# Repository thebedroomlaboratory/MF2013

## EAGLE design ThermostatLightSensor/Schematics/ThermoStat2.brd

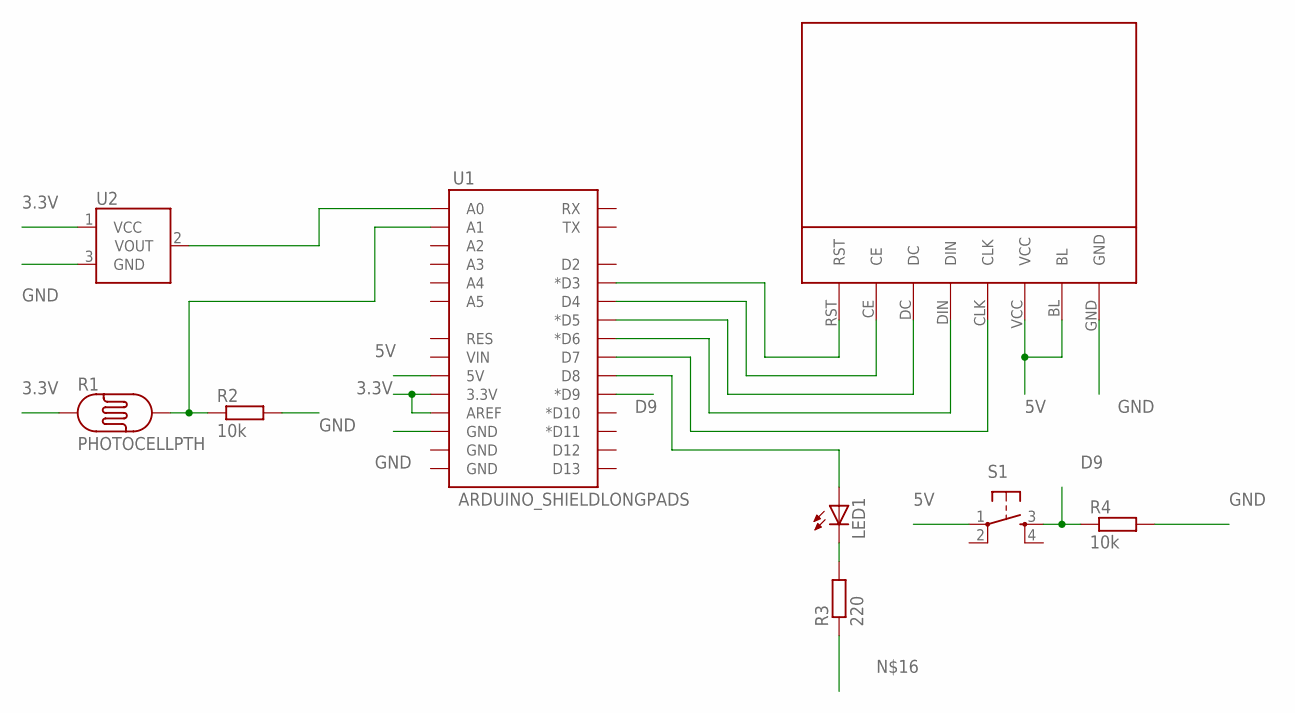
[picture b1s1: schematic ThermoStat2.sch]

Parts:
LED1: LED5MM
R1: PHOTOCELLPTH; PHOTOCELL
R2, R4: 10k; 0207/15
R3: 220; 0207/15
S1: TAC_SWITCHPTH; TACTILE-PTH
U1: ARDUINO_SHIELDLONGPADS; DUEMILANOVE_SHIELD_LONGPADS
U2: TMP36GT9; TO-92
U$1: NOKIA5510

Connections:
3.3V: R1.1, U1.3.3V, U1.AREF, U2.1 (VCC)
5V: S1.1, U1.5V, U$1.BL, U$1.VCC
D9: R4.1, S1.3, U1.D9 (*D9)
GND: R2.2, R4.2, U1.GND@2 (GND), U2.3 (GND), U$1.GND
unnamed: R1.2, R2.1, U1.A1
unnamed: U1.A0, U2.2 (VOUT)
unnamed: U1.D3 (*D3), U$1.RST
unnamed: U1.D4, U$1.CE
unnamed: U1.D5 (*D5), U$1.DC
unnamed: U1.D6 (*D6), U$1.DIN
unnamed: U1.D7, U$1.CLK
unnamed: LED1.K (C), R3.2
unnamed: LED1.A, U1.D8

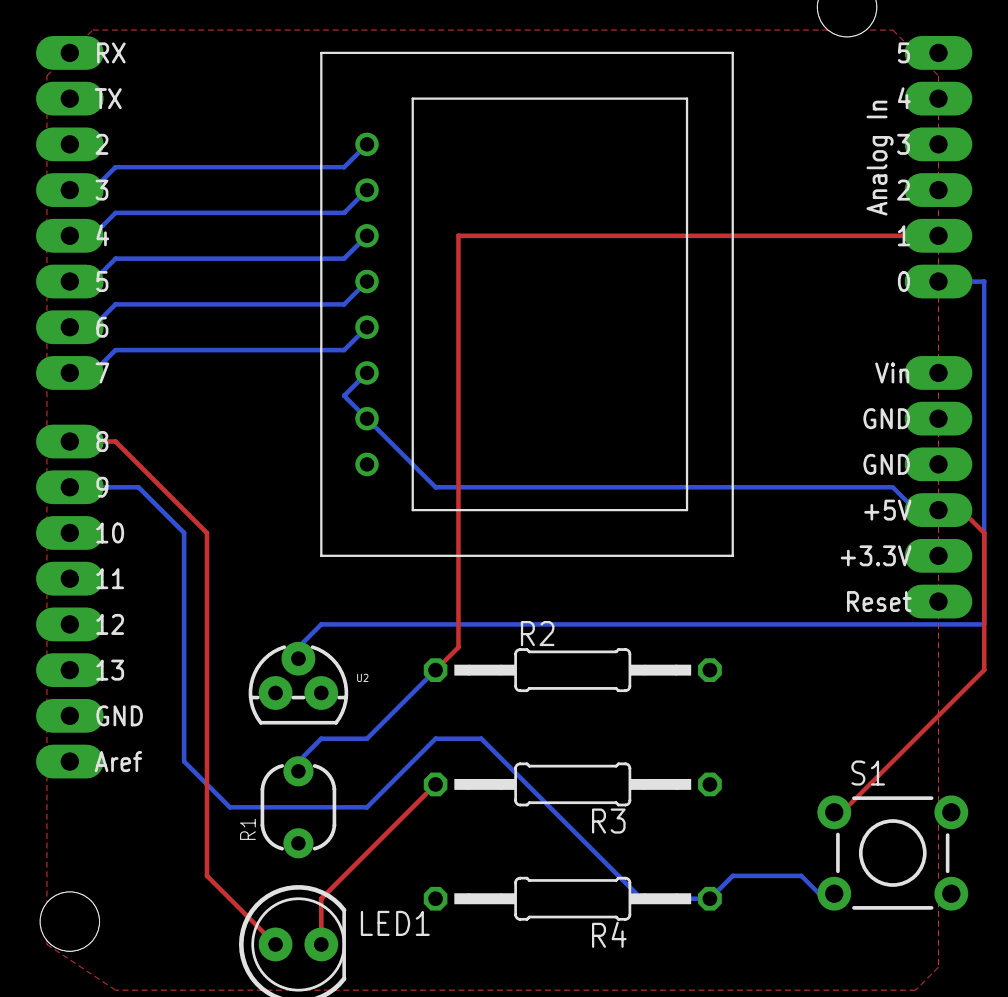
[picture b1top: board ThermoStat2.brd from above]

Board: 2 copper layers, 9 parts (0 on the bottom side), 13 nets.

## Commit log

2013-07-13 First
2013-07-13 Directories added
2013-07-13 added a test file
2013-07-13 Test commit
2013-07-13 test2
2013-07-13 test3
2013-07-13 added a project overview image
2013-07-13 Sample arduino sketch for serial communication
2013-07-14 Test program for serial
2013-07-14 Files for arduino code and schematic
2013-07-14 All variables for serial with multiple arduinos configured
2013-07-14 Update for Serial Output
2013-07-14 light&temp
2013-07-14 Toggel buttons with webSocket Comms
    the Index page includes 3 slider buttons which commuinicate to python
    via webSockets to send a 3 digit binary number
2013-07-14 Update to appease Martin
2013-07-14 added Service Folder
2013-07-14 Socket Service added
2013-07-14 partial clean
2013-07-14 full clean
2013-07-14 Socket Service, seperated message into individual variables for heating, lighting and oven status
2013-07-14 Thermostat arduino sketch finished
2013-07-15 changed structure and added data access
2013-07-16 SocketService.py - cleaned up and removed unnecessary code
    Removed unnecessary code not needed
2013-07-16 Updated Index.html
    removed JavaScript to external file, cleaned up formatting, added class "socketSwitch" to onofswitch inputs
2013-07-16 Update maker.js
    added on document ready function to attach action Listener to the inputs of class "socketSwitch"
2013-07-16 Create controlCenter.js
    extracted control center functions to separate script to allow more modular design
2013-07-16 Update index.html
    added controlCenter.js
2013-07-16 Update SocketService.py
    Added a validate method to prevent invalid values being passed
2013-07-16 #1 Persisted the data read into the database, not tested
2013-07-16 added check for when a serial reading is complete
2013-07-16 #1 added images demonstrating working with issues
2013-07-16 #1 highlighted some relevant parts of an issue image
2013-07-17 File added so that connections between serial and logic can be made
2013-07-17 Added a very rough script for setting up Ubuntu 12.04 for this project It would be better to run the commands from this script individually.
2013-07-20 #1 Tweaked the SerialTest which now works with one Arduino, TODO Test with all 3
2013-07-21 Now transport information via JSON
2013-07-21 Modified arduino test sketch to take serial input
2013-07-21 Added image for design of website
2013-07-21 #2 Added control logic and serial output to turn stuff on/off
2013-07-21 Chart.js
2013-07-21 Update maker.js
    Added Chart and Light functions
2013-07-21 Create home.html
    a rough version of final page including a charts, light an control functions
2013-07-21 Create light.css
    css for the light indicator widget
2013-07-21 #4 Extracting data from JavaScript socket connection and linking to control logic. Still needs to be tidied.
2013-07-22 Read from database and convert output to JSON
2013-07-22 #4 #2 Fixed threading issues with Tornado server, improved the control logic and renamed the main program app.
2013-07-23 Adding files for people counter arduino sketch. Still needs major revision.
2013-07-23 #5 Renamed variables and deleted code for screen in people counter sketch
2013-07-23 #4 Code for checking on different Arduino IDE version
2013-07-23 Updated maker.js
    functions in updateCCInfo() are currently hardcoded, as are the populateGraphs() and timer() functions. These need to interact with service in next update
2013-07-23 Updated home.html inline with maker.js
2013-07-23 Update main.css with rough layout and styling (Needs a lot more work)
2013-07-23 #5 Program for people counter with direction running perfectly. Needs to be soldered and tested though.
2013-07-24 #5 Edited code to reduce number of pins used so that we can make an arduino shield. Also added logo stencil.
2013-07-25 Added logic for handling the physical override button on the thermostat. Also, switched to using deepcopy function in order to keep historical values.
2013-07-25 #6 Tidying up files for bagel oven sketch so that libraries will work on any computer
2013-07-25 #1 tested 2 and put in code for all 3. TODO test 3
2013-07-25 Home page with working graph with real data
2013-07-26 Posters added.
2013-07-26 Update home2.php
    combined home.html update with php
2013-07-26 Lets make things a little more sexy
2013-07-26 adding bg.jpg
2013-07-26 adding font
2013-07-26 #10 add refresh to home page
2013-07-26 #10 auto refresh database
2013-07-26 home2 some update that I dont know
2013-07-26 added missing functions to maker2.js
2013-07-27 #10 backup home page
2013-07-27 POC of get request from server
2013-07-27 Speedometer graph for light
2013-07-27 #10 Yeah boy.

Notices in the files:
parts and their libraries:
SparkFun-Boards: Licensing: CC v3.0 Share-Alike You are welcome to use this library for commercial purposes.
